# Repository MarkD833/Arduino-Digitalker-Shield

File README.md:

# Arduino UNO National Semiconductor Digitalker Shield
I recently discovered a National Semiconductor Digitalker IC in my collection. This one is packaged in a yellow box supplied by RS Componenets in the UK. I also have 2 of the Digitalker speech ROMS.

Now I'm more confident with using Eagle PCB (v7.7.0) and producing gerbers for JLCPCB I figured I'd have a go at producing a Digitalker shield for an Arduino UNO.

My main inspiration for this project is a web page published by [Dr. Scott M. Baker](https://www.smbaker.com/this-is-digitalker-and-jameco-je520-too-vintage-speech-synthesis) and the recent discovery of quite a few Digitalker ROMs that had been uploaded the the [Internet Archive](https://archive.org/details/digitalker).

You can read more about the Digitalker chip on [Dr. Scott M. Baker's](https://www.smbaker.com/this-is-digitalker-and-jameco-je520-too-vintage-speech-synthesis) web page.

## Description

The aim of this project is to create a shield for an Arduino UNO to bring to life a Digitalker speech IC and to have a large non-volatile storage device to store the contents of several speech ROMs in.

## Design

In order to speak a word (or phrase or sound), the Digitalker chip needs to know which word to speak and this is defined by the binary value on the SW1 (LSB) to SW8 (MSB) inputs of the Digitalker chip.

There's also Chip Select (/CS) which in a minimum configuration can be grounded along with the Command Select (/CMS) signal.

Finally, there is the Write Strobe (/WR) which initiates the generation of the speech on the rising edge.

### Word Selection

The Digitialker chip has 14 address lines (A0..A13) to address up to 16Kbytes of storage. The original speech ROMs had a storage capacity of 8Kbytes each. Address line A13 was used to select the lower or upper ROM. The lower ROM CS signal was active low whereas the upper ROM CS signal was active high.

I'm using an AM29F040B flash chip with a capacity of 512Kbytes to store the contents of the various speech ROMs currently available.

### Interface

I've chosen to use the SPI interface of the ATMEGA328P on the UNO and a couple of 74HCT595 serial-in / parallel-out shift registers to transfer information to the Digitalker chip. One shift register is dedicated to providing the 8-bit word number to speak. The other shift register handles address lines A14..A18 of the flash chip in order to select the pair of speech ROMs required.

I'm using the SPI signals MOSI and SCK from the ICSP header on the UNO rather than D11 and D13 in the hope that this board can also be used with an Arduino MEGA2560 as well. The SPI signals on the Arduino MEGA2560 board are on completely different pins, but they are also present on the ICSP header in the same physical location as on the UNO.

The SPI SS signal is routed to the D10 pin on the UNO and the Write Strobe is routed to the A1 pin on the UNO. The Digitalker chip has an interrupt pin which goes high to tell the host that the chosen word/phrase has been spoken. I've routed this to the A0 pin on the UNO. 

### Power

The Digitalker chip requires a supply voltage of between 7V and 11V. I'm not a power supply designer so I used an off the shelf DC/DC boost module designed around the SDB628 IC and configured its output for 9V.

### Audio

I'm also not an audio designer so I used an off the shelf audio amplifier module - HXJ8002 - to handle the audio amplification.

# Assembly

Start with the SMD components - there are a few resistors and capacitors which should be easy to hand solder. Then add the various IC sockets and the header pins.

I mounted the DC/DC convertor and the audio module on pin headers so I could easily remove them if necessary.

When you've installed all the basic components, then before fitting any chips, check that you have 9V on the VCC pin of the Digitalker chip. These chips are rare and expensive to replace so best to check first.

Install the rest of the chips, excluding the flash memory as you will need to program it with your chosen speech ROMs. 

# Programming the speech ROMs

The speech ROMs are generally designed to be used in pairs.

As a basic check, start with the SSR1 & SSR2 ROMs. The files for these ROMs were named SSR1.bin and SSR2.bin in the archive I used.

Using a PROM programmer of your choice, load the SSR1.bin file into memory starting at address 0x0000. Next, load the SSR2.bin file but this time you need to make sure that it is loaded into your PROM programmer memory starting at address 0x2000. Add the SSR5.bin and SSR6.bin files as well if you want to.

The memory map in your PROM programmer should be similar to this if you also want to include the SSR5 & SSR6 ROMs as well:

 | ROM Bank | ROM 1 | ROM 2 |
 | -------- | ----- | ----- |
 | 0        | SSR1.bin (0000-1FFF) | SSR2.bin (2000-3FFF) |
 | 1        | SSR5.bin (4000-5FFF) | SSR6.bin (6000-7FFF) |
 
Then program the flash chip with the loaded data and install it in your board.

# Speaking the first words

Digitalker has it's own equivalent of [Hello World](https://en.wikipedia.org/wiki/%22Hello,_World!%22_program). With the SSR1 and SSR2 ROMs programmed into the flash chip, word number 0 is the phrase "THIS IS DIGITALKER".

I've created a simple test sketch that you can use to speak any word in any ROM.

The commands are entered into the Arduino IDE serial monitor. There are only 2 commands:
* n : a number, for example - 0, 1 or 25 to speek word or phrase associated with that number
* Rn : R followed by a number will switch ROM sets - R2 switches to ROM set #2. Any words or phrases will now come from ROM set #2.

# Further information

Have a look in the datasheets folder for information on the Digitalker chips.

| Kit ID | Description |
| --- | --- |
| DT1000 | Speech synthesis evaluation board |
| DT1050(3) | Standard vocabulary kit - details the words in ROMs SSR1 & SSR2 |
| DT1051(4) | Speech evaluation kit - details the words in ROMs SSR3 & SSR4 |
| DT1052(5) | Basic numbers kit |
| DT1056(7) | Standard vocabulary kit - details the words in ROMs SSR5 & SSR6 |
| DTSW-500  | Digitalker vocabulary selection system (DVSS) (CP/M 2.2 application) |

The SSR3 and SSR4 ROMs have yet to be found despite the best searches of other Digitalker enthusiasts. However, the DT1051 / DT1054 datasheet does list the phrases that are programmed into the SSR3 and SSR4 ROMs.

The user manual for the DVSS also is proving elusive. The SSR3 and SSR4 ROMs could potentially be recreated using the DVSS software as the datasheet indicates that the DVSS software includes 500 words that could be used to create custom ROMs.

# DVSS software user guide

I've spent a bit of time with my RC2014 CP/M system and had the chance to experiment with the DVSS software. I've found out how to use it and even how to create my own ROMs for the Digitalker chip to use.

I've put everything I've discovered into a [separate repository here](https://github.com/MarkD833/Digitalker-Digital-Voice-Selection-Software).

## Version History

* 0.1
    * Initial Release

## License

This project is licensed under the GNU General Public License v3.0 - see the LICENSE.md file for details

## Acknowledgments

Inspiration etc.
* [Dr. Scott M. Baker](https://www.smbaker.com/this-is-digitalker-and-jameco-je520-too-vintage-speech-synthesis)
* George de Bouter

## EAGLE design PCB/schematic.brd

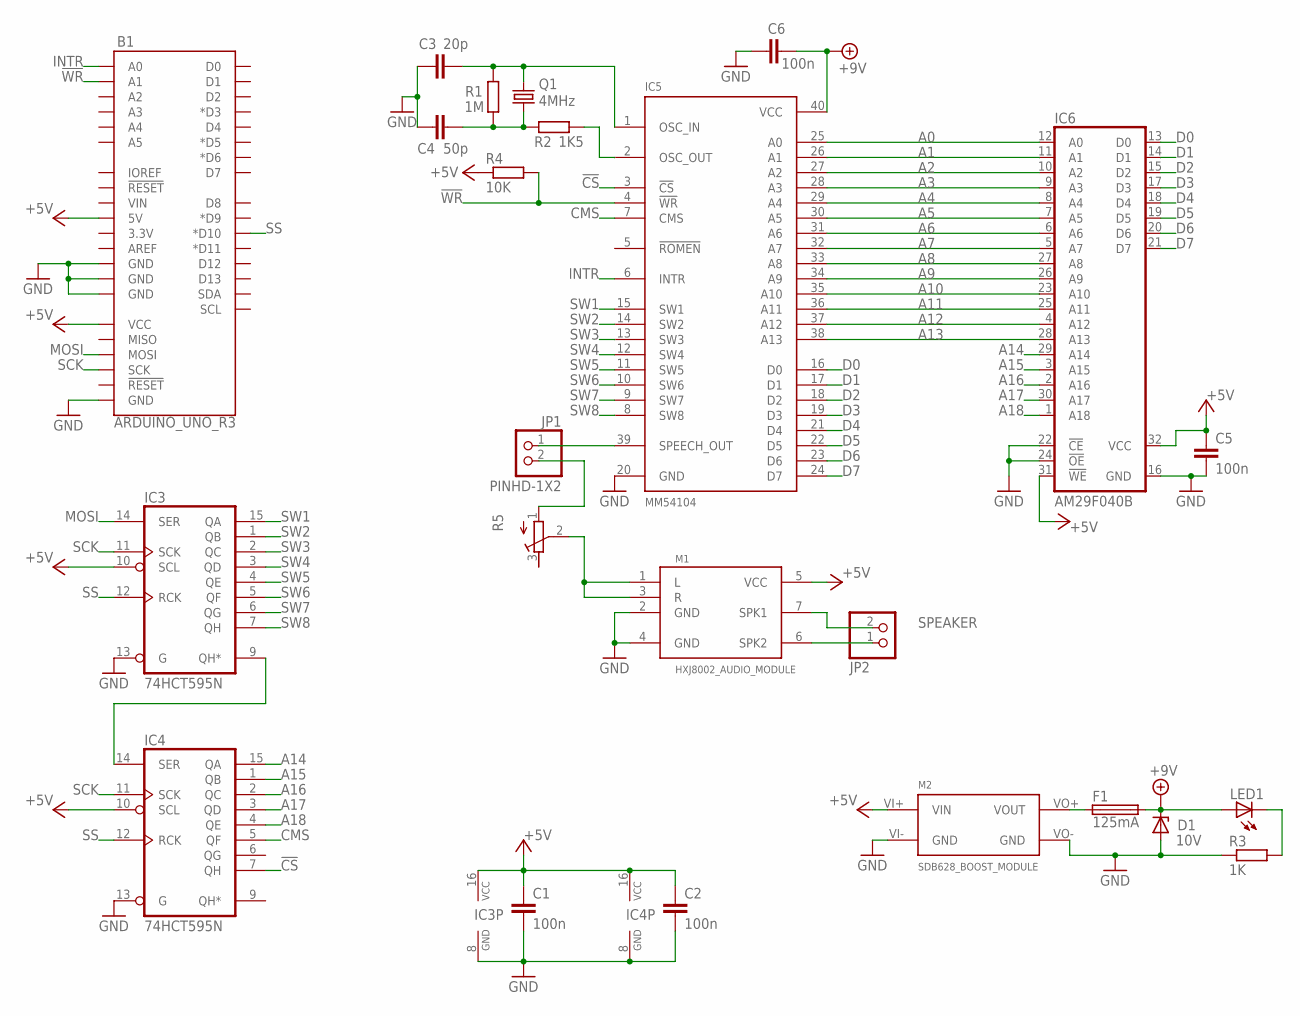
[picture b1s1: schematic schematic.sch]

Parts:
B1: ARDUINO_UNO_R3; ARDUINO_R3
C1, C2, C5, C6: 100n; C0805K
C3: 20p; C0805K
C4: 50p; C0805K
D1: 10V; F126Z12
F1: 125mA; TE5
IC3, IC4: 74HCT595N; DIL16
IC5: MM54104; DIL40
IC6: AM29F040B; PLCC32
JP1: PINHD-1X2; 1X02
JP2: PINHD-1X2/90; 1X02/90
LED1: LEDCHIPLED_1206; CHIPLED_1206
M1: HXJ8002_AUDIO_MODULE; HXJ8002
M2: SDB628_BOOST_MODULE; SDB628_MODULE
Q1: 4MHz; HC49/S
R1: 1M; R0805
R2: 1K5; R0805
R3: 1K; R0805W
R4: 10K; R0805W
R5: R-TRIMM3296W; RTRIM3296W

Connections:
!CS: IC4.7 (QH), IC5.3 (!CS)
!WR: B1.A1, IC5.4 (!WR), R4.2
+5V: B1.5V, B1.VCC, C1.1, C2.1, C5.1, IC3.10 (SCL), IC3.16 (VCC), IC4.10 (SCL), IC4.16 (VCC), IC6.31 (!WE), IC6.32 (VCC), M1.5 (VCC), M2.VI+ (VIN), R4.1
+9V: C6.2, D1.C, F1.2, IC5.40 (VCC), LED1.A
A0: IC5.25 (A0), IC6.12 (A0)
A1: IC5.26 (A1), IC6.11 (A1)
A2: IC5.27 (A2), IC6.10 (A2)
A3: IC5.28 (A3), IC6.9 (A3)
A4: IC5.29 (A4), IC6.8 (A4)
A5: IC5.30 (A5), IC6.7 (A5)
A6: IC5.31 (A6), IC6.6 (A6)
A7: IC5.32 (A7), IC6.5 (A7)
A8: IC5.33 (A8), IC6.27 (A8)
A9: IC5.34 (A9), IC6.26 (A9)
A10: IC5.35 (A10), IC6.23 (A10)
A11: IC5.36 (A11), IC6.25 (A11)
A12: IC5.37 (A12), IC6.4 (A12)
A13: IC5.38 (A13), IC6.28 (A13)
A14: IC4.15 (QA), IC6.29 (A14)
A15: IC4.1 (QB), IC6.3 (A15)
A16: IC4.2 (QC), IC6.2 (A16)
A17: IC4.3 (QD), IC6.30 (A17)
A18: IC4.4 (QE), IC6.1 (A18)
CMS: IC4.5 (QF), IC5.7 (CMS)
D0: IC5.16 (D0), IC6.13 (D0)
D1: IC5.17 (D1), IC6.14 (D1)
D2: IC5.18 (D2), IC6.15 (D2)
D3: IC5.19 (D3), IC6.17 (D3)
D4: IC5.21 (D4), IC6.18 (D4)
D5: IC5.22 (D5), IC6.19 (D5)
D6: IC5.23 (D6), IC6.20 (D6)
D7: IC5.24 (D7), IC6.21 (D7)
GND: B1.GND@1 (GND), B1.GND@2 (GND), B1.GND@3 (GND), B1.GND@4 (GND), C1.2, C2.2, C3.1, C4.1, C5.2, C6.1, D1.A, IC3.8 (GND), IC3.13 (G), IC4.8 (GND), IC4.13 (G), IC5.20 (GND), IC6.16 (GND), IC6.22 (!CE), IC6.24 (!OE), M1.2 (GND), M1.4 (GND), M2.VI- (GND), M2.VO- (GND), R3.1
INTR: B1.A0, IC5.6 (INTR)
MOSI: B1.MOSI, IC3.14 (SER)
unnamed: IC3.9 (QH*), IC4.14 (SER)
unnamed: JP2.1, M1.6 (SPK2)
unnamed: C4.2, Q1.1, R1.1, R2.1
unnamed: C3.2, IC5.1 (OSC_IN), Q1.2, R1.2
unnamed: IC5.2 (OSC_OUT), R2.2
unnamed: M1.1 (L), M1.3 (R), R5.2 (S)
unnamed: IC5.39 (SPEECH_OUT), JP1.1
unnamed: JP2.2, M1.7 (SPK1)
unnamed: F1.1, M2.VO+ (VOUT)
unnamed: JP1.2, R5.1 (A)
unnamed: LED1.C, R3.2
SCK: B1.SCK, IC3.11 (SCK), IC4.11 (SCK)
SS: B1.D10 (*D10), IC3.12 (RCK), IC4.12 (RCK)
SW1: IC3.15 (QA), IC5.15 (SW1)
SW2: IC3.1 (QB), IC5.14 (SW2)
SW3: IC3.2 (QC), IC5.13 (SW3)
SW4: IC3.3 (QD), IC5.12 (SW4)
SW5: IC3.4 (QE), IC5.11 (SW5)
SW6: IC3.5 (QF), IC5.10 (SW6)
SW7: IC3.6 (QG), IC5.9 (SW7)
SW8: IC3.7 (QH), IC5.8 (SW8)

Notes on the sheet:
SPEAKER

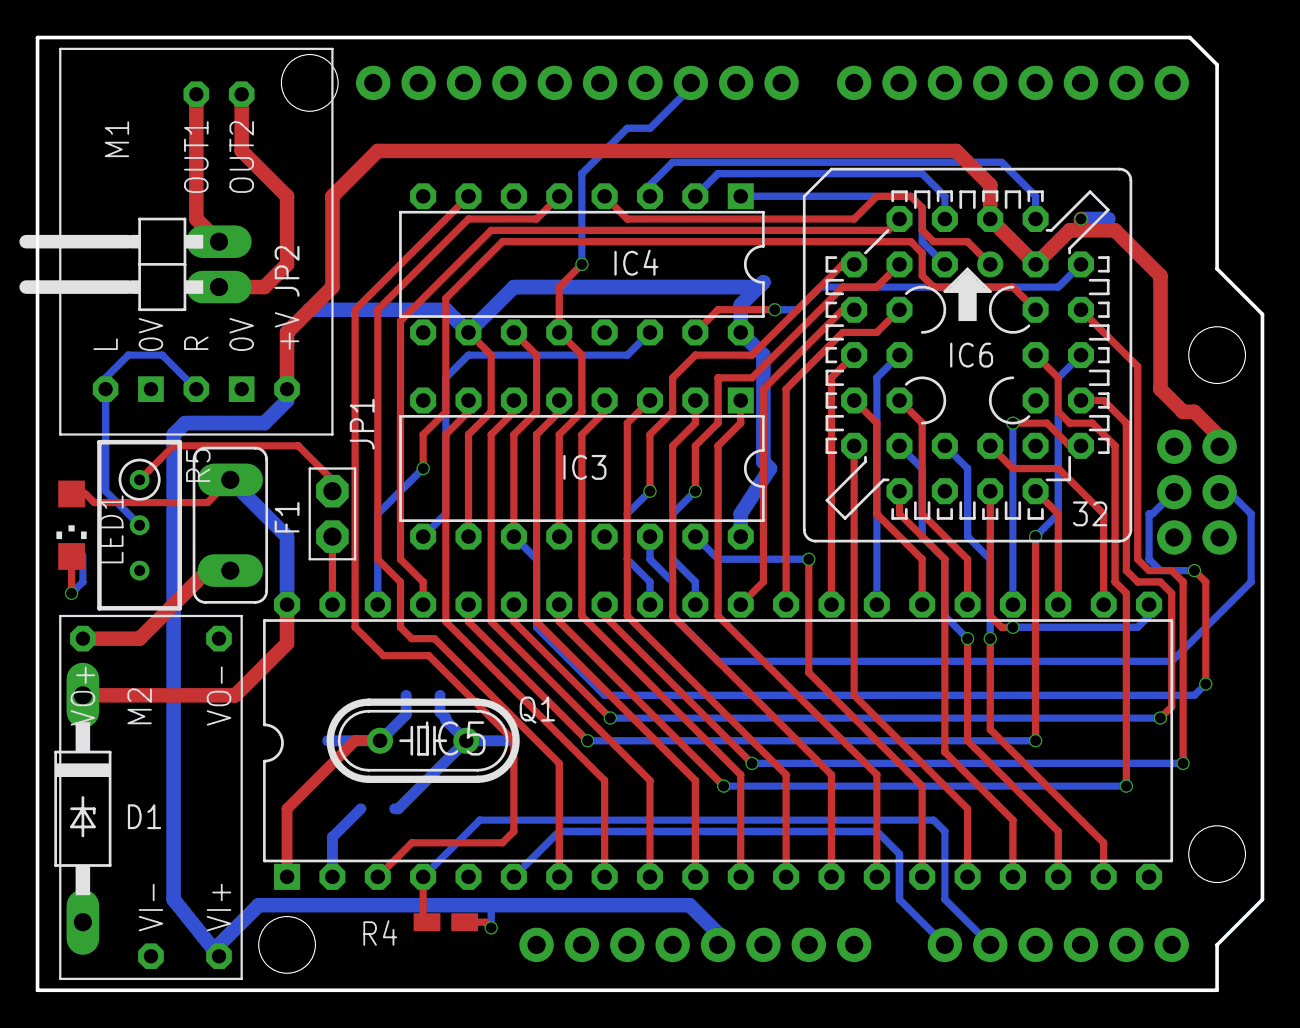
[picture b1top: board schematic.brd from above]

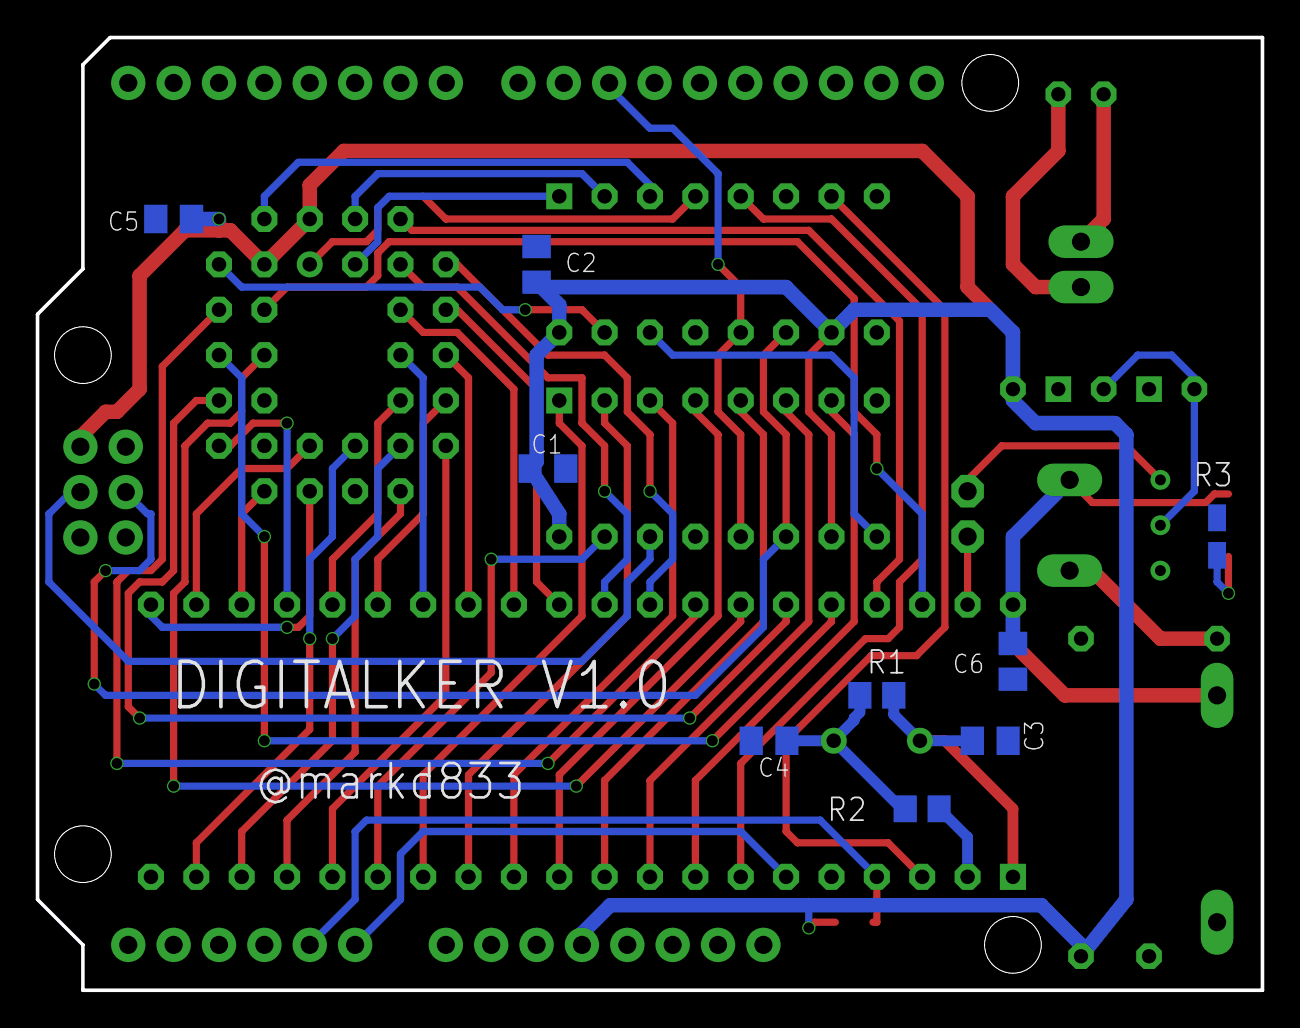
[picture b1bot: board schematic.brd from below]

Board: 2 copper layers, 68.6 x 53.3 mm, 24 parts (9 on the bottom side), 56 nets.

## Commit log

2023-12-04 added PCB design
